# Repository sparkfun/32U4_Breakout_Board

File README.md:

ATMEGA32U4 Breakout Board
=========================

[ 
*ATMEGA32U4 Breakout Board (DEV-11117)*](https://www.sparkfun.com/products/11117)

This breakout board is designed for folks who would like to program outside of the Arduino IDE. THe board
comes preloaded with the LUFA CDC bootloader, allowing code to be built in WinAVR and program the board over USB
using AVRDUDE. 

Repository Contents
-------------------
* **/Bootloaders** - CDC bootloader and instructions for installation
* **/Examples** - Example code for the board
* **/Hardware** - All Eagle design files (.brd, .sch)
* **/LUFA** - Instructions for setting up the LUFA bootloader

License Information
-------------------
The hardware is released under [Creative Commons Share-alike 3.0](http://creativecommons.org/licenses/by-sa/3.0/).  
All other code is open source so please feel free to do anything you want with it; you buy me a beer if you use this and we meet someday ([Beerware license](http://en.wikipedia.org/wiki/Beerware)).

Notes for Installation
----------------------
This directory contains the bootloader and example source files for
Sparkfun's 32u4 Breakout board. Both were built on WinXP sp3 with
WinAVR-20100110 and AVRDUDE 5.10.

The bootloader is a modified LUFA-130303 CDC bootloader.

The bootloader directory contains the source and hex file for the bootloader
that ships with this board.  When you first plug in the board to a Windows
machine, it will ask you for a driver.  Point it to the following directory:
\SFE_32U4_Breakout_Board\Bootloaders\CDC
It will find the driver file (LUFA CDC Bootloader.inf) there.

Once your machine recognizes the Virtual COM port, you're ready to take a
look at the examples and try uploading them to your board. See the readme in
the examples directory for more information.

Before you can build any projects, you'll need to download and install
WinAVR if you're using Windows. It can be found [here](http://sourceforge.net/projects/winavr/files/). 

Linux Users
-----------
You will need to install the following packages:
* **avr-gcc** - A port of the GNU C compiler to the AVR Architecture
* **avr-binutils** - Converts the object code into AVR-readable hex files
* **avr-libc** - AVR Library for stuff like accessing and manipulating registers
* **avrdude** - The software that actually drives the physical programming

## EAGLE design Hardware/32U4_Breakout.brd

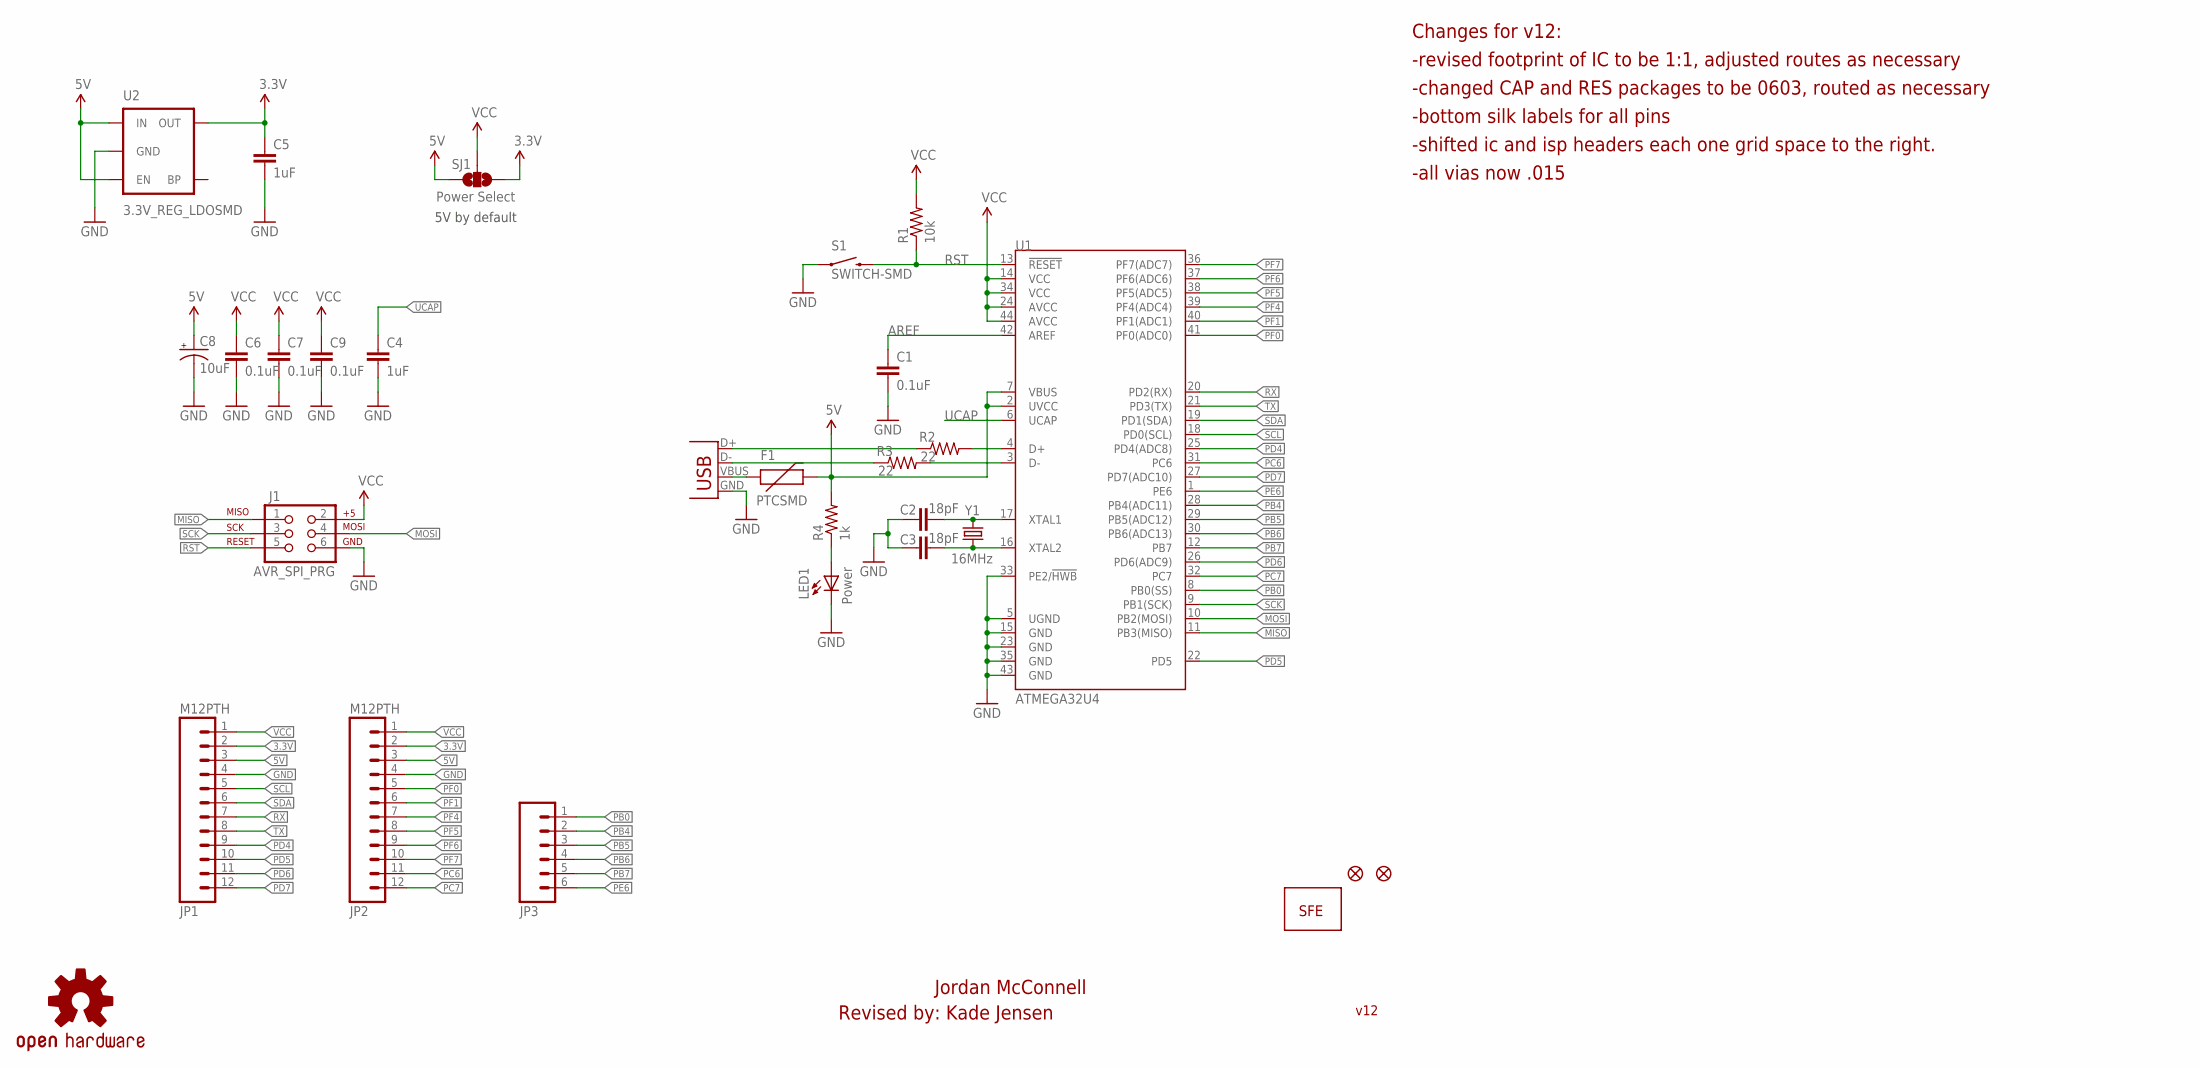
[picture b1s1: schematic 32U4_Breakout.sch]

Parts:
C1, C6, C7, C9: 0.1uF; 0603-CAP
C2, C3: 18pF; 0603-CAP
C4, C5: 1uF; 0603-CAP
C8: 10uF; EIA3216
F1: PTCSMD; PTC-1206
J1: AVR_SPI_PRG; 2X3
JP1, JP2: M12PTH; 1X12
JP3: M06SIP; 1X06
JP6, JP7: FIDUCIAL1X2; FIDUCIAL-1X2
JP8: LOGO-SFENEW; SFE-NEW-WEBLOGO
LED1: Power; LED-0603
R1: 10k; 0603-RES
R2, R3: 22; 0603-RES
R4: 1k; 0603-RES
S1: SWITCH-SMD; TACTILE_SWITCH_SMD
SJ1: Power Select; SJ_3_PASTE2&3
U1: ATMEGA32U4; QFN-44-NOPAD_1:1
U2: 3.3V_REG_LDOSMD; SOT23-5
U$6: OSHW-LOGOM; OSHW-LOGO-M
X1: USBSMD; USB-MINIB
Y1: 16MHz; CRYSTAL-SMD-5X3

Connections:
3.3V: C5.1, JP1.2, JP2.2, SJ1.1, U2.5 (OUT)
5V: C8.A (+), F1.2, JP1.3, JP2.3, R4.2, SJ1.3, U1.2 (UVCC), U1.7 (VBUS), U2.1 (IN), U2.3 (EN)
AREF: C1.1, U1.42 (AREF)
D+: R2.1, X1.D+
D-: R3.1, X1.D-
GND: C1.2, C2.1, C3.1, C4.2, C5.2, C6.2, C7.2, C8.C (-), C9.2, J1.6, JP1.4, JP2.4, LED1.C, S1.1, U1.5 (UGND), U1.15 (GND), U1.23 (GND), U1.33 (PE2/!HWB), U1.35 (GND), U1.43 (GND), U2.2 (GND), X1.GND
MISO: J1.1, U1.11 (PB3(MISO))
MOSI: J1.4, U1.10 (PB2(MOSI))
unnamed: C2.2, U1.17 (XTAL1), Y1.3 (2)
unnamed: C3.2, U1.16 (XTAL2), Y1.1
unnamed: F1.1, X1.VBUS
unnamed: R2.2, U1.4 (D+)
unnamed: R3.2, U1.3 (D-)
unnamed: LED1.A, R4.1
PB0: JP3.1, U1.8 (PB0(SS))
PB4: JP3.2, U1.28 (PB4(ADC11))
PB5: JP3.3, U1.29 (PB5(ADC12))
PB6: JP3.4, U1.30 (PB6(ADC13))
PB7: JP3.5, U1.12 (PB7)
PC6: JP2.11, U1.31 (PC6)
PC7: JP2.12, U1.32 (PC7)
PD4: JP1.9, U1.25 (PD4(ADC8))
PD5: JP1.10, U1.22 (PD5)
PD6: JP1.11, U1.26 (PD6(ADC9))
PD7: JP1.12, U1.27 (PD7(ADC10))
PE6: JP3.6, U1.1 (PE6)
PF0: JP2.5, U1.41 (PF0(ADC0))
PF1: JP2.6, U1.40 (PF1(ADC1))
PF4: JP2.7, U1.39 (PF4(ADC4))
PF5: JP2.8, U1.38 (PF5(ADC5))
PF6: JP2.9, U1.37 (PF6(ADC6))
PF7: JP2.10, U1.36 (PF7(ADC7))
RST: J1.5, R1.1, S1.3 (2), U1.13 (!RESET)
RX: JP1.7, U1.20 (PD2(RX))
SCK: J1.3, U1.9 (PB1(SCK))
SCL: JP1.5, U1.18 (PD0(SCL))
SDA: JP1.6, U1.19 (PD1(SDA))
TX: JP1.8, U1.21 (PD3(TX))
UCAP: C4.1, U1.6 (UCAP)
VCC: C6.1, C7.1, C9.1, J1.2, JP1.1, JP2.1, R1.2, SJ1.2, U1.14 (VCC), U1.24 (AVCC), U1.34 (VCC), U1.44 (AVCC)

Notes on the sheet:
Changes for v12:
-revised footprint of IC to be 1:1, adjusted routes as necessary
-changed CAP and RES packages to be 0603, routed as necessary
-bottom silk labels for all pins
-shifted ic and isp headers each one grid space to the right.
Jordan McConnell
Revised by: Kade Jensen
-all vias now .015
5V by default
v12

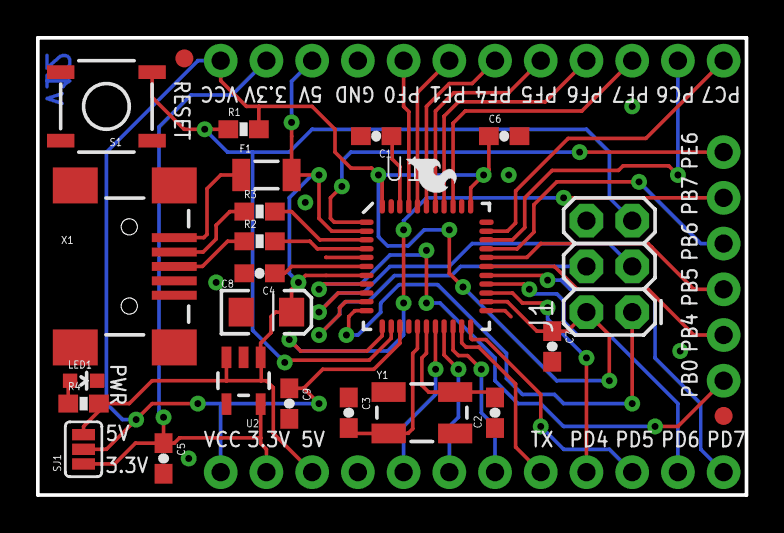
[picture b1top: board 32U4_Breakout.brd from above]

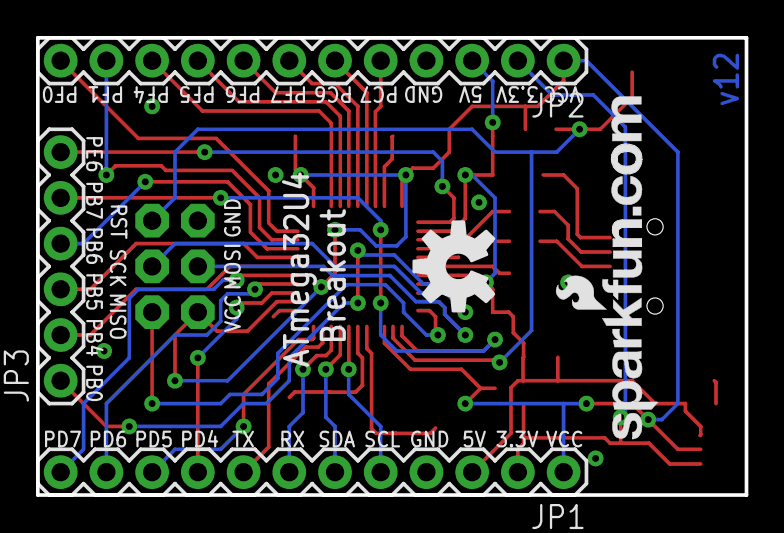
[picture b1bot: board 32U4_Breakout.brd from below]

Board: 2 copper layers, 39.4 x 25.4 mm, 30 parts (5 on the bottom side), 40 nets.

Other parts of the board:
JP5: LOGO-SFESK; SFE-LOGO-FLAME

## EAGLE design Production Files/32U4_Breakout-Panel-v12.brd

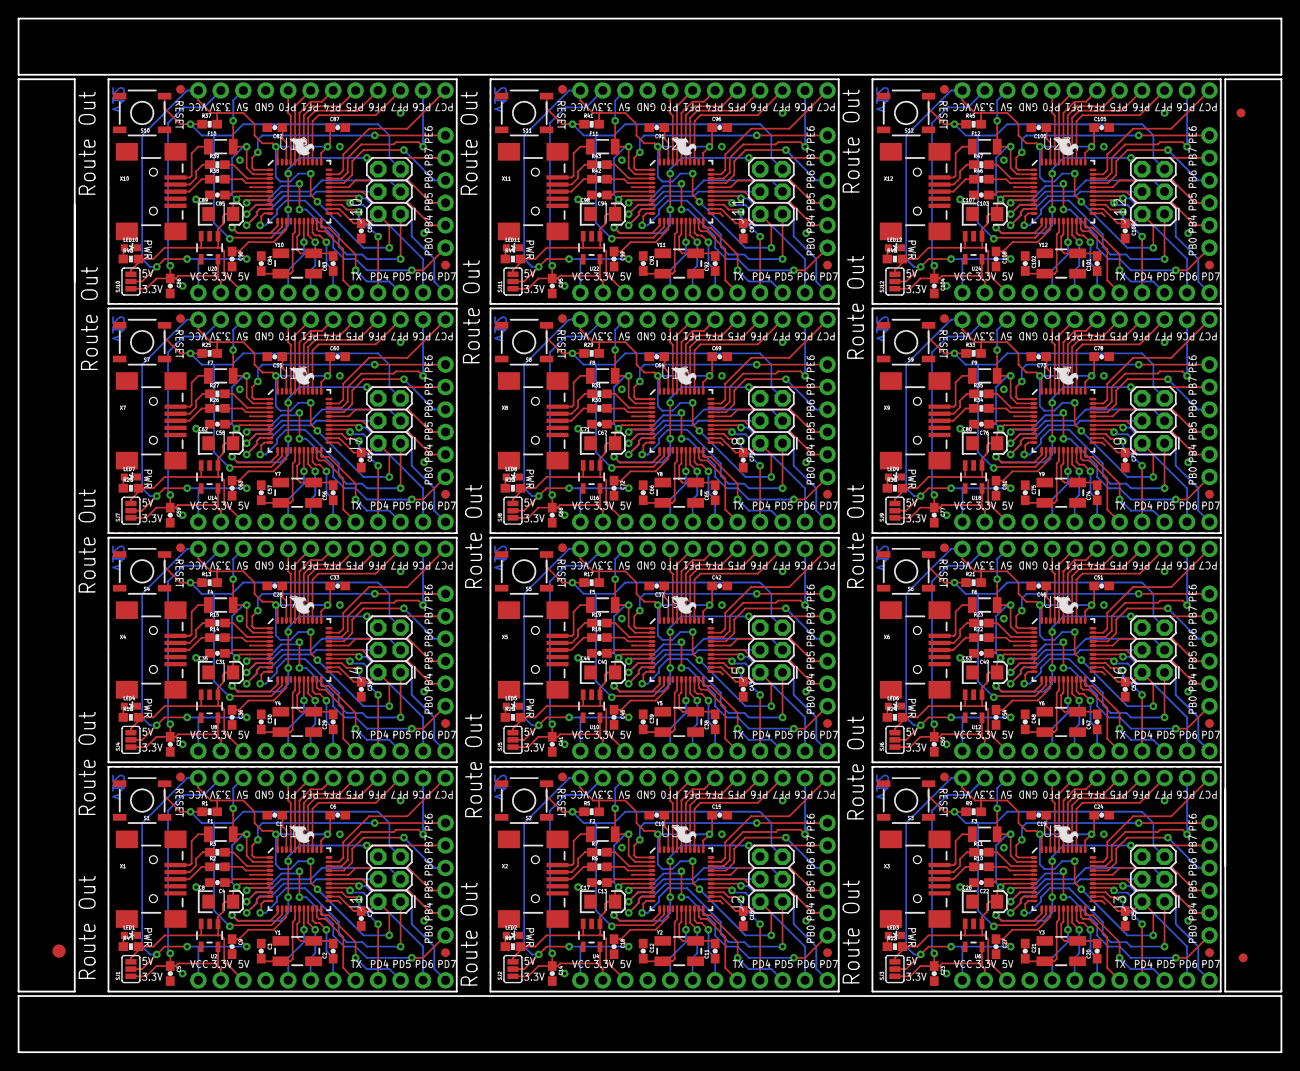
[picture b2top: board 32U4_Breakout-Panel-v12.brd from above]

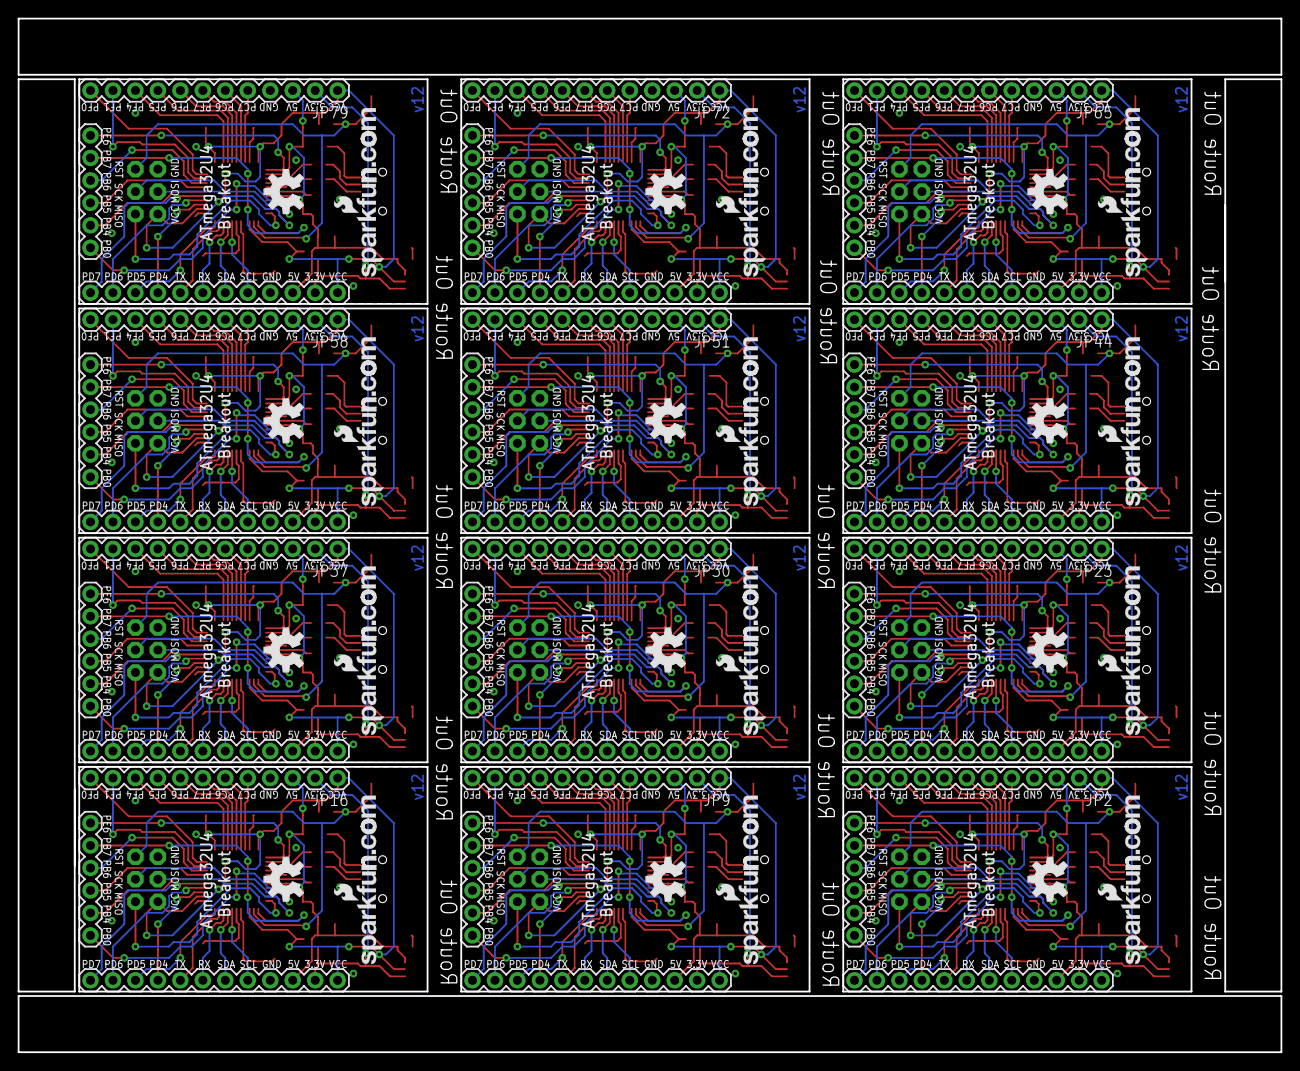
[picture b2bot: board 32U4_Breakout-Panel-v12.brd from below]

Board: 2 copper layers, 142.7 x 116.8 mm, 363 parts (60 on the bottom side), 480 nets.

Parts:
C1, C6, C7, C9, C10, C15, C16, C18, C19, C24, C25, C27, C28, C33, C34, C36, C37, C42, C43, C45, C46, C51, C52, C54, C55, C60, C61, C63, C64, C69, C70, C72, C73, C78, C79, C81, C82, C87, C88, C90, C91, C96, C97, C99, C100, C105, C106, C108: 0.1uF; 0603-CAP
C2, C3, C11, C12, C20, C21, C29, C30, C38, C39, C47, C48, C56, C57, C65, C66, C74, C75, C83, C84, C92, C93, C101, C102: 18pF; 0603-CAP
C4, C5, C13, C14, C22, C23, C31, C32, C40, C41, C49, C50, C58, C59, C67, C68, C76, C77, C85, C86, C94, C95, C103, C104: 1uF; 0603-CAP
C8, C17, C26, C35, C44, C53, C62, C71, C80, C89, C98, C107: 10uF; EIA3216
E$1: FIDUCIAL-1.5X3
E$4, E$5: FIDUCIAL-1X2
F1, F2, F3, F4, F5, F6, F7, F8, F9, F10, F11, F12: PTCSMD; PTC-1206
J1, J2, J3, J4, J5, J6, J7, J8, J9, J10, J11, J12: AVR_SPI_PRG; 2X3
JP1, JP2, JP4, JP9, JP15, JP16, JP22, JP23, JP29, JP30, JP36, JP37, JP43, JP44, JP50, JP51, JP57, JP58, JP64, JP65, JP71, JP72, JP78, JP79: M12PTH; 1X12
JP3, JP10, JP17, JP24, JP31, JP38, JP45, JP52, JP59, JP66, JP73, JP80: 1X06
JP5, JP11, JP18, JP25, JP32, JP39, JP46, JP53, JP60, JP67, JP74, JP81: LOGO-SFESK; SFE-LOGO-FLAME
JP6, JP7, JP12, JP13, JP19, JP20, JP26, JP27, JP33, JP34, JP40, JP41, JP47, JP48, JP54, JP55, JP61, JP62, JP68, JP69, JP75, JP76, JP82, JP83: FIDUCIAL1X2; FIDUCIAL-1X2
JP8, JP14, JP21, JP28, JP35, JP42, JP49, JP56, JP63, JP70, JP77, JP84: LOGO-SFENEW; SFE-NEW-WEBLOGO
LED1, LED2, LED3, LED4, LED5, LED6, LED7, LED8, LED9, LED10, LED11, LED12: Power; LED-0603
R1, R5, R9, R13, R17, R21, R25, R29, R33, R37, R41, R45: 10k; 0603-RES
R2, R3, R6, R7, R10, R11, R14, R15, R18, R19, R22, R23, R26, R27, R30, R31, R34, R35, R38, R39, R42, R43, R46, R47: 22; 0603-RES
R4, R8, R12, R16, R20, R24, R28, R32, R36, R40, R44, R48: 1k; 0603-RES
S1, S2, S3, S4, S5, S6, S7, S8, S9, S10, S11, S12: SWITCH-SMD; TACTILE_SWITCH_SMD
SJ1, SJ2, SJ3, SJ4, SJ5, SJ6, SJ7, SJ8, SJ9, SJ10, SJ11, SJ12: Power Select; SJ_3_PASTE2&3
U1, U3, U5, U7, U9, U11, U13, U15, U17, U19, U21, U23: ATMEGA32U4; QFN-44-NOPAD_1:1-LESS_PASTE
U2, U4, U6, U8, U10, U12, U14, U16, U18, U20, U22, U24: 3.3V_REG_LDOSMD; SOT23-5
U$1, U$2, U$3, U$4, U$5, U$6, U$7, U$8, U$9, U$10, U$11, U$12: OSHW-LOGOM; OSHW-LOGO-M
X1, X2, X3, X4, X5, X6, X7, X8, X9, X10, X11, X12: USBSMD; USB-MINIB
Y1, Y2, Y3, Y4, Y5, Y6, Y7, Y8, Y9, Y10, Y11, Y12: 16MHz; CRYSTAL-SMD-5X3

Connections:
3.3V: C5.1, JP1.2, JP2.2, SJ1.1, U2.5
3.3V1: C14.1, JP4.2, JP9.2, SJ2.1, U4.5
3.3V2: C23.1, JP15.2, JP16.2, SJ3.1, U6.5
3.3V3: C32.1, JP22.2, JP23.2, SJ4.1, U8.5
3.3V4: C41.1, JP29.2, JP30.2, SJ5.1, U10.5
3.3V5: C50.1, JP36.2, JP37.2, SJ6.1, U12.5
3.3V6: C59.1, JP43.2, JP44.2, SJ7.1, U14.5
3.3V7: C68.1, JP50.2, JP51.2, SJ8.1, U16.5
3.3V8: C77.1, JP57.2, JP58.2, SJ9.1, U18.5
3.3V9: C86.1, JP64.2, JP65.2, SJ10.1, U20.5
3.3V10: C95.1, JP71.2, JP72.2, SJ11.1, U22.5
3.3V11: C104.1, JP78.2, JP79.2, SJ12.1, U24.5
5V: C8.A, F1.2, JP1.3, JP2.3, R4.2, SJ1.3, U1.2, U1.7, U2.1, U2.3
5V1: C17.A, F2.2, JP4.3, JP9.3, R8.2, SJ2.3, U3.2, U3.7, U4.1, U4.3
5V2: C26.A, F3.2, JP15.3, JP16.3, R12.2, SJ3.3, U5.2, U5.7, U6.1, U6.3
5V3: C35.A, F4.2, JP22.3, JP23.3, R16.2, SJ4.3, U7.2, U7.7, U8.1, U8.3
5V4: C44.A, F5.2, JP29.3, JP30.3, R20.2, SJ5.3, U9.2, U9.7, U10.1, U10.3
5V5: C53.A, F6.2, JP36.3, JP37.3, R24.2, SJ6.3, U11.2, U11.7, U12.1, U12.3
5V6: C62.A, F7.2, JP43.3, JP44.3, R28.2, SJ7.3, U13.2, U13.7, U14.1, U14.3
5V7: C71.A, F8.2, JP50.3, JP51.3, R32.2, SJ8.3, U15.2, U15.7, U16.1, U16.3
5V8: C80.A, F9.2, JP57.3, JP58.3, R36.2, SJ9.3, U17.2, U17.7, U18.1, U18.3
5V9: C89.A, F10.2, JP64.3, JP65.3, R40.2, SJ10.3, U19.2, U19.7, U20.1, U20.3
5V10: C98.A, F11.2, JP71.3, JP72.3, R44.2, SJ11.3, U21.2, U21.7, U22.1, U22.3
5V11: C107.A, F12.2, JP78.3, JP79.3, R48.2, SJ12.3, U23.2, U23.7, U24.1, U24.3
AREF: C1.1, U1.42
AREF1: C10.1, U3.42
AREF2: C19.1, U5.42
AREF3: C28.1, U7.42
AREF4: C37.1, U9.42
AREF5: C46.1, U11.42
AREF6: C55.1, U13.42
AREF7: C64.1, U15.42
AREF8: C73.1, U17.42
AREF9: C82.1, U19.42
AREF10: C91.1, U21.42
AREF11: C100.1, U23.42
D+: R2.1, X1.D+
D+1: R6.1, X2.D+
D+2: R10.1, X3.D+
D+3: R14.1, X4.D+
D+4: R18.1, X5.D+
D+5: R22.1, X6.D+
D+6: R26.1, X7.D+
D+7: R30.1, X8.D+
D+8: R34.1, X9.D+
D+9: R38.1, X10.D+
D+10: R42.1, X11.D+
D+11: R46.1, X12.D+
D-: R3.1, X1.D-
D-1: R7.1, X2.D-
D-2: R11.1, X3.D-
D-3: R15.1, X4.D-
D-4: R19.1, X5.D-
D-5: R23.1, X6.D-
D-6: R27.1, X7.D-
D-7: R31.1, X8.D-
D-8: R35.1, X9.D-
D-9: R39.1, X10.D-
D-10: R43.1, X11.D-
D-11: R47.1, X12.D-
GND: C1.2, C2.1, C3.1, C4.2, C5.2, C6.2, C7.2, C8.C, C9.2, J1.6, JP1.4, JP2.4, LED1.C, S1.1, U1.5, U1.15, U1.23, U1.33, U1.35, U1.43, U2.2, X1.GND
GND1: C10.2, C11.1, C12.1, C13.2, C14.2, C15.2, C16.2, C17.C, C18.2, J2.6, JP4.4, JP9.4, LED2.C, S2.1, U3.5, U3.15, U3.23, U3.33, U3.35, U3.43, U4.2, X2.GND
GND2: C19.2, C20.1, C21.1, C22.2, C23.2, C24.2, C25.2, C26.C, C27.2, J3.6, JP15.4, JP16.4, LED3.C, S3.1, U5.5, U5.15, U5.23, U5.33, U5.35, U5.43, U6.2, X3.GND
GND3: C28.2, C29.1, C30.1, C31.2, C32.2, C33.2, C34.2, C35.C, C36.2, J4.6, JP22.4, JP23.4, LED4.C, S4.1, U7.5, U7.15, U7.23, U7.33, U7.35, U7.43, U8.2, X4.GND
GND4: C37.2, C38.1, C39.1, C40.2, C41.2, C42.2, C43.2, C44.C, C45.2, J5.6, JP29.4, JP30.4, LED5.C, S5.1, U9.5, U9.15, U9.23, U9.33, U9.35, U9.43, U10.2, X5.GND
GND5: C46.2, C47.1, C48.1, C49.2, C50.2, C51.2, C52.2, C53.C, C54.2, J6.6, JP36.4, JP37.4, LED6.C, S6.1, U11.5, U11.15, U11.23, U11.33, U11.35, U11.43, U12.2, X6.GND
GND6: C55.2, C56.1, C57.1, C58.2, C59.2, C60.2, C61.2, C62.C, C63.2, J7.6, JP43.4, JP44.4, LED7.C, S7.1, U13.5, U13.15, U13.23, U13.33, U13.35, U13.43, U14.2, X7.GND
GND7: C64.2, C65.1, C66.1, C67.2, C68.2, C69.2, C70.2, C71.C, C72.2, J8.6, JP50.4, JP51.4, LED8.C, S8.1, U15.5, U15.15, U15.23, U15.33, U15.35, U15.43, U16.2, X8.GND
GND8: C73.2, C74.1, C75.1, C76.2, C77.2, C78.2, C79.2, C80.C, C81.2, J9.6, JP57.4, JP58.4, LED9.C, S9.1, U17.5, U17.15, U17.23, U17.33, U17.35, U17.43, U18.2, X9.GND
GND9: C82.2, C83.1, C84.1, C85.2, C86.2, C87.2, C88.2, C89.C, C90.2, J10.6, JP64.4, JP65.4, LED10.C, S10.1, U19.5, U19.15, U19.23, U19.33, U19.35, U19.43, U20.2, X10.GND
GND10: C91.2, C92.1, C93.1, C94.2, C95.2, C96.2, C97.2, C98.C, C99.2, J11.6, JP71.4, JP72.4, LED11.C, S11.1, U21.5, U21.15, U21.23, U21.33, U21.35, U21.43, U22.2, X11.GND
GND11: C100.2, C101.1, C102.1, C103.2, C104.2, C105.2, C106.2, C107.C, C108.2, J12.6, JP78.4, JP79.4, LED12.C, S12.1, U23.5, U23.15, U23.23, U23.33, U23.35, U23.43, U24.2, X12.GND
MISO: J1.1, U1.11
MISO1: J2.1, U3.11
MISO2: J3.1, U5.11
MISO3: J4.1, U7.11
MISO4: J5.1, U9.11
MISO5: J6.1, U11.11
MISO6: J7.1, U13.11
MISO7: J8.1, U15.11
MISO8: J9.1, U17.11
MISO9: J10.1, U19.11
MISO10: J11.1, U21.11
MISO11: J12.1, U23.11
MOSI: J1.4, U1.10
MOSI1: J2.4, U3.10
MOSI2: J3.4, U5.10
MOSI3: J4.4, U7.10
MOSI4: J5.4, U9.10
MOSI5: J6.4, U11.10
MOSI6: J7.4, U13.10
MOSI7: J8.4, U15.10
MOSI8: J9.4, U17.10
MOSI9: J10.4, U19.10
MOSI10: J11.4, U21.10
MOSI11: J12.4, U23.10
unnamed: C11.2, U3.17, Y2.3
unnamed: C2.2, U1.17, Y1.3
unnamed: C3.2, U1.16, Y1.1
unnamed: F1.1, X1.VBUS
unnamed: C12.2, U3.16, Y2.1
unnamed: R2.2, U1.4
unnamed: R6.2, U3.4
unnamed: R3.2, U1.3
unnamed: LED1.A, R4.1
unnamed: R7.2, U3.3
unnamed: F2.1, X2.VBUS
unnamed: LED2.A, R8.1
unnamed: C20.2, U5.17, Y3.3
unnamed: C21.2, U5.16, Y3.1
unnamed: R10.2, U5.4
unnamed: R11.2, U5.3
unnamed: F3.1, X3.VBUS
unnamed: LED3.A, R12.1
unnamed: C29.2, U7.17, Y4.3
unnamed: C30.2, U7.16, Y4.1
unnamed: R14.2, U7.4
unnamed: R15.2, U7.3
unnamed: F4.1, X4.VBUS
unnamed: LED4.A, R16.1
unnamed: C38.2, U9.17, Y5.3
unnamed: C39.2, U9.16, Y5.1
unnamed: R18.2, U9.4
unnamed: R19.2, U9.3
unnamed: F5.1, X5.VBUS
unnamed: LED5.A, R20.1
unnamed: C47.2, U11.17, Y6.3
unnamed: C48.2, U11.16, Y6.1
unnamed: R22.2, U11.4
unnamed: R23.2, U11.3
unnamed: F6.1, X6.VBUS
unnamed: LED6.A, R24.1
unnamed: C56.2, U13.17, Y7.3
unnamed: C57.2, U13.16, Y7.1
unnamed: R26.2, U13.4
unnamed: R27.2, U13.3
unnamed: F7.1, X7.VBUS
unnamed: LED7.A, R28.1
unnamed: C65.2, U15.17, Y8.3
unnamed: C66.2, U15.16, Y8.1
unnamed: R30.2, U15.4
unnamed: R31.2, U15.3
unnamed: F8.1, X8.VBUS
unnamed: LED8.A, R32.1
unnamed: C74.2, U17.17, Y9.3
unnamed: C75.2, U17.16, Y9.1
unnamed: R34.2, U17.4
unnamed: R35.2, U17.3
unnamed: F9.1, X9.VBUS
unnamed: LED9.A, R36.1
unnamed: C83.2, U19.17, Y10.3
unnamed: C84.2, U19.16, Y10.1
unnamed: R38.2, U19.4
unnamed: R39.2, U19.3
unnamed: F10.1, X10.VBUS
unnamed: LED10.A, R40.1
unnamed: C92.2, U21.17, Y11.3
unnamed: C93.2, U21.16, Y11.1
unnamed: R42.2, U21.4
unnamed: R43.2, U21.3
unnamed: F11.1, X11.VBUS
unnamed: LED11.A, R44.1
unnamed: C101.2, U23.17, Y12.3
unnamed: C102.2, U23.16, Y12.1
unnamed: R46.2, U23.4
unnamed: R47.2, U23.3
unnamed: F12.1, X12.VBUS
unnamed: LED12.A, R48.1
PB0: JP3.1, U1.8
PB1: JP10.2, U3.28
PB2: JP10.3, U3.29
PB3: JP10.4, U3.30
PB4: JP3.2, U1.28
PB5: JP3.3, U1.29
PB6: JP3.4, U1.30
PB7: JP3.5, U1.12
PB8: JP10.5, U3.12
PB9: JP10.1, U3.8
PB10: JP17.2, U5.28
PB11: JP17.3, U5.29
PB12: JP17.4, U5.30
PB13: JP17.5, U5.12
PB14: JP17.1, U5.8
PB15: JP24.2, U7.28
PB16: JP24.3, U7.29
PB17: JP24.4, U7.30
PB18: JP24.5, U7.12
PB19: JP24.1, U7.8
PB20: JP31.2, U9.28
PB21: JP31.3, U9.29
PB22: JP31.4, U9.30
PB23: JP31.5, U9.12
PB24: JP31.1, U9.8
PB25: JP38.2, U11.28
PB26: JP38.3, U11.29
PB27: JP38.4, U11.30
PB28: JP38.5, U11.12
PB29: JP38.1, U11.8
PB30: JP45.2, U13.28
PB31: JP45.3, U13.29
PB32: JP45.4, U13.30
PB33: JP45.5, U13.12
PB34: JP45.1, U13.8
PB35: JP52.2, U15.28
PB36: JP52.3, U15.29
PB37: JP52.4, U15.30
PB38: JP52.5, U15.12
PB39: JP52.1, U15.8
PB40: JP59.2, U17.28
PB41: JP59.3, U17.29
PB42: JP59.4, U17.30
PB43: JP59.5, U17.12
PB44: JP59.1, U17.8
PB45: JP66.2, U19.28
PB46: JP66.3, U19.29
PB47: JP66.4, U19.30
PB48: JP66.5, U19.12
PB49: JP66.1, U19.8
PB50: JP73.2, U21.28
PB51: JP73.3, U21.29
PB52: JP73.4, U21.30
PB53: JP73.5, U21.12
PB54: JP73.1, U21.8
PB55: JP80.2, U23.28
PB56: JP80.3, U23.29
PB57: JP80.4, U23.30
PB58: JP80.5, U23.12
PB59: JP80.1, U23.8
PC1: JP9.11, U3.31
PC2: JP9.12, U3.32
PC3: JP16.11, U5.31
PC4: JP16.12, U5.32
PC5: JP23.11, U7.31
PC6: JP2.11, U1.31
PC7: JP2.12, U1.32
PC8: JP23.12, U7.32
PC9: JP30.11, U9.31
PC10: JP30.12, U9.32
PC11: JP37.11, U11.31
PC12: JP37.12, U11.32
PC13: JP44.11, U13.31
PC14: JP44.12, U13.32
PC15: JP51.11, U15.31
PC16: JP51.12, U15.32
PC17: JP58.11, U17.31
PC18: JP58.12, U17.32
PC19: JP65.11, U19.31
PC20: JP65.12, U19.32
PC21: JP72.11, U21.31
PC22: JP72.12, U21.32
PC23: JP79.11, U23.31
PC24: JP79.12, U23.32
PD1: JP4.9, U3.25
PD2: JP4.12, U3.27
PD3: JP4.11, U3.26
PD4: JP1.9, U1.25
PD5: JP1.10, U1.22
PD6: JP1.11, U1.26
PD7: JP1.12, U1.27
PD8: JP4.10, U3.22
PD9: JP15.9, U5.25
PD10: JP15.12, U5.27
PD11: JP15.11, U5.26
PD12: JP15.10, U5.22
PD13: JP22.9, U7.25
PD14: JP22.12, U7.27
PD15: JP22.11, U7.26
PD16: JP22.10, U7.22
PD17: JP29.9, U9.25
PD18: JP29.12, U9.27
PD19: JP29.11, U9.26
PD20: JP29.10, U9.22
PD21: JP36.9, U11.25
PD22: JP36.12, U11.27
PD23: JP36.11, U11.26
PD24: JP36.10, U11.22
PD25: JP43.9, U13.25
PD26: JP43.12, U13.27
PD27: JP43.11, U13.26
PD28: JP43.10, U13.22
PD29: JP50.9, U15.25
PD30: JP50.12, U15.27
PD31: JP50.11, U15.26
PD32: JP50.10, U15.22
PD33: JP57.9, U17.25
PD34: JP57.12, U17.27
PD35: JP57.11, U17.26
PD36: JP57.10, U17.22
PD37: JP64.9, U19.25
PD38: JP64.12, U19.27
PD39: JP64.11, U19.26
PD40: JP64.10, U19.22
PD41: JP71.9, U21.25
PD42: JP71.12, U21.27
PD43: JP71.11, U21.26
PD44: JP71.10, U21.22
PD45: JP78.9, U23.25
PD46: JP78.12, U23.27
PD47: JP78.11, U23.26
PD48: JP78.10, U23.22
PE1: JP10.6, U3.1
PE2: JP17.6, U5.1
PE3: JP24.6, U7.1
PE4: JP31.6, U9.1
PE5: JP38.6, U11.1
PE6: JP3.6, U1.1
PE7: JP45.6, U13.1
PE8: JP52.6, U15.1
PE9: JP59.6, U17.1
PE10: JP66.6, U19.1
PE11: JP73.6, U21.1
PE12: JP80.6, U23.1
PF0: JP2.5, U1.41
PF1: JP2.6, U1.40
PF2: JP9.10, U3.36
PF3: JP9.9, U3.37
PF4: JP2.7, U1.39
PF5: JP2.8, U1.38
PF6: JP2.9, U1.37
PF7: JP2.10, U1.36
PF8: JP9.8, U3.38
PF9: JP9.7, U3.39
PF10: JP9.6, U3.40
PF11: JP9.5, U3.41
PF12: JP16.10, U5.36
PF13: JP16.9, U5.37
PF14: JP16.8, U5.38
PF15: JP16.7, U5.39
PF16: JP16.6, U5.40
PF17: JP16.5, U5.41
PF18: JP23.10, U7.36
PF19: JP23.9, U7.37
PF20: JP23.8, U7.38
PF21: JP23.7, U7.39
PF22: JP23.6, U7.40
PF23: JP23.5, U7.41
PF24: JP30.10, U9.36
PF25: JP30.9, U9.37
PF26: JP30.8, U9.38
PF27: JP30.7, U9.39
PF28: JP30.6, U9.40
PF29: JP30.5, U9.41
PF30: JP37.10, U11.36
PF31: JP37.9, U11.37
PF32: JP37.8, U11.38
PF33: JP37.7, U11.39
PF34: JP37.6, U11.40
PF35: JP37.5, U11.41
PF36: JP44.10, U13.36
PF37: JP44.9, U13.37
PF38: JP44.8, U13.38
PF39: JP44.7, U13.39
PF40: JP44.6, U13.40
PF41: JP44.5, U13.41
PF42: JP51.10, U15.36
PF43: JP51.9, U15.37
PF44: JP51.8, U15.38
PF45: JP51.7, U15.39
PF46: JP51.6, U15.40
PF47: JP51.5, U15.41
PF48: JP58.10, U17.36
PF49: JP58.9, U17.37
PF50: JP58.8, U17.38
PF51: JP58.7, U17.39
PF52: JP58.6, U17.40
PF53: JP58.5, U17.41
PF54: JP65.10, U19.36
PF55: JP65.9, U19.37
PF56: JP65.8, U19.38
PF57: JP65.7, U19.39
PF58: JP65.6, U19.40
PF59: JP65.5, U19.41
PF60: JP72.10, U21.36
PF61: JP72.9, U21.37
PF62: JP72.8, U21.38
PF63: JP72.7, U21.39
PF64: JP72.6, U21.40
PF65: JP72.5, U21.41
PF66: JP79.10, U23.36
PF67: JP79.9, U23.37
PF68: JP79.8, U23.38
PF69: JP79.7, U23.39
PF70: JP79.6, U23.40
PF71: JP79.5, U23.41
RST: J1.5, R1.1, S1.3, U1.13
RST1: J2.5, R5.1, S2.3, U3.13
RST2: J3.5, R9.1, S3.3, U5.13
RST3: J4.5, R13.1, S4.3, U7.13
RST4: J5.5, R17.1, S5.3, U9.13
RST5: J6.5, R21.1, S6.3, U11.13
RST6: J7.5, R25.1, S7.3, U13.13
RST7: J8.5, R29.1, S8.3, U15.13
RST8: J9.5, R33.1, S9.3, U17.13
RST9: J10.5, R37.1, S10.3, U19.13
RST10: J11.5, R41.1, S11.3, U21.13
RST11: J12.5, R45.1, S12.3, U23.13
RX: JP1.7, U1.20
RX1: JP4.7, U3.20
RX2: JP15.7, U5.20
RX3: JP22.7, U7.20
RX4: JP29.7, U9.20
RX5: JP36.7, U11.20
RX6: JP43.7, U13.20
RX7: JP50.7, U15.20
RX8: JP57.7, U17.20
RX9: JP64.7, U19.20
RX10: JP71.7, U21.20
RX11: JP78.7, U23.20
SCK: J1.3, U1.9
SCK1: J2.3, U3.9
SCK2: J3.3, U5.9
SCK3: J4.3, U7.9
SCK4: J5.3, U9.9
SCK5: J6.3, U11.9
SCK6: J7.3, U13.9
SCK7: J8.3, U15.9
SCK8: J9.3, U17.9
SCK9: J10.3, U19.9
SCK10: J11.3, U21.9
SCK11: J12.3, U23.9
SCL: JP1.5, U1.18
SCL1: JP4.5, U3.18
SCL2: JP15.5, U5.18
SCL3: JP22.5, U7.18
SCL4: JP29.5, U9.18
SCL5: JP36.5, U11.18
SCL6: JP43.5, U13.18
SCL7: JP50.5, U15.18
SCL8: JP57.5, U17.18
SCL9: JP64.5, U19.18
SCL10: JP71.5, U21.18
SCL11: JP78.5, U23.18
SDA: JP1.6, U1.19
SDA1: JP4.6, U3.19
SDA2: JP15.6, U5.19
SDA3: JP22.6, U7.19
SDA4: JP29.6, U9.19
SDA5: JP36.6, U11.19
SDA6: JP43.6, U13.19
SDA7: JP50.6, U15.19
SDA8: JP57.6, U17.19
SDA9: JP64.6, U19.19
SDA10: JP71.6, U21.19
SDA11: JP78.6, U23.19
TX: JP1.8, U1.21
TX1: JP4.8, U3.21
TX2: JP15.8, U5.21
TX3: JP22.8, U7.21
TX4: JP29.8, U9.21
TX5: JP36.8, U11.21
TX6: JP43.8, U13.21
TX7: JP50.8, U15.21
TX8: JP57.8, U17.21
TX9: JP64.8, U19.21
TX10: JP71.8, U21.21
TX11: JP78.8, U23.21
UCAP: C4.1, U1.6
UCAP1: C13.1, U3.6
UCAP2: C22.1, U5.6
UCAP3: C31.1, U7.6
UCAP4: C40.1, U9.6
UCAP5: C49.1, U11.6
UCAP6: C58.1, U13.6
UCAP7: C67.1, U15.6
UCAP8: C76.1, U17.6
UCAP9: C85.1, U19.6
UCAP10: C94.1, U21.6
UCAP11: C103.1, U23.6
VCC: C6.1, C7.1, C9.1, J1.2, JP1.1, JP2.1, R1.2, SJ1.2, U1.14, U1.24, U1.34, U1.44
VCC1: C15.1, C16.1, C18.1, J2.2, JP4.1, JP9.1, R5.2, SJ2.2, U3.14, U3.24, U3.34, U3.44
VCC2: C24.1, C25.1, C27.1, J3.2, JP15.1, JP16.1, R9.2, SJ3.2, U5.14, U5.24, U5.34, U5.44
VCC3: C33.1, C34.1, C36.1, J4.2, JP22.1, JP23.1, R13.2, SJ4.2, U7.14, U7.24, U7.34, U7.44
VCC4: C42.1, C43.1, C45.1, J5.2, JP29.1, JP30.1, R17.2, SJ5.2, U9.14, U9.24, U9.34, U9.44
VCC5: C51.1, C52.1, C54.1, J6.2, JP36.1, JP37.1, R21.2, SJ6.2, U11.14, U11.24, U11.34, U11.44
VCC6: C60.1, C61.1, C63.1, J7.2, JP43.1, JP44.1, R25.2, SJ7.2, U13.14, U13.24, U13.34, U13.44
VCC7: C69.1, C70.1, C72.1, J8.2, JP50.1, JP51.1, R29.2, SJ8.2, U15.14, U15.24, U15.34, U15.44
VCC8: C78.1, C79.1, C81.1, J9.2, JP57.1, JP58.1, R33.2, SJ9.2, U17.14, U17.24, U17.34, U17.44
VCC9: C87.1, C88.1, C90.1, J10.2, JP64.1, JP65.1, R37.2, SJ10.2, U19.14, U19.24, U19.34, U19.44
VCC10: C96.1, C97.1, C99.1, J11.2, JP71.1, JP72.1, R41.2, SJ11.2, U21.14, U21.24, U21.34, U21.44
VCC11: C105.1, C106.1, C108.1, J12.2, JP78.1, JP79.1, R45.2, SJ12.2, U23.14, U23.24, U23.34, U23.44

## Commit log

2012-06-01 readme commit
2012-06-01 adding LUFA folder
2012-06-01 Initial commit with source/hex files
2013-03-20 Updated bootloader to use LUFA 130303
2013-09-23 Added Hardware folder with Eagle files
    Added board and schematic files for v11.
2013-09-23 Updated to v12 eagle files
    Eagle files for QC board revision and schematic updates.
2013-10-23 Moved C5 and a couple tarces
    Moved C5 and a couple traces to prevent problems with top silk on the
    vcc jumper.
2013-10-25 Panel Created
    normal sized panel for now.
2013-12-12 Updating READMEs and cleaning up repo
2014-05-14 Fix line endings
2014-05-14 changed paste layer on IC

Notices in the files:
parts and their libraries:
SparkFun-Capacitors: Licensing: CC v3.0 Share-Alike You are welcome to use this library for commercial purposes.
SparkFun-Aesthetics: Released under the Creative Commons
